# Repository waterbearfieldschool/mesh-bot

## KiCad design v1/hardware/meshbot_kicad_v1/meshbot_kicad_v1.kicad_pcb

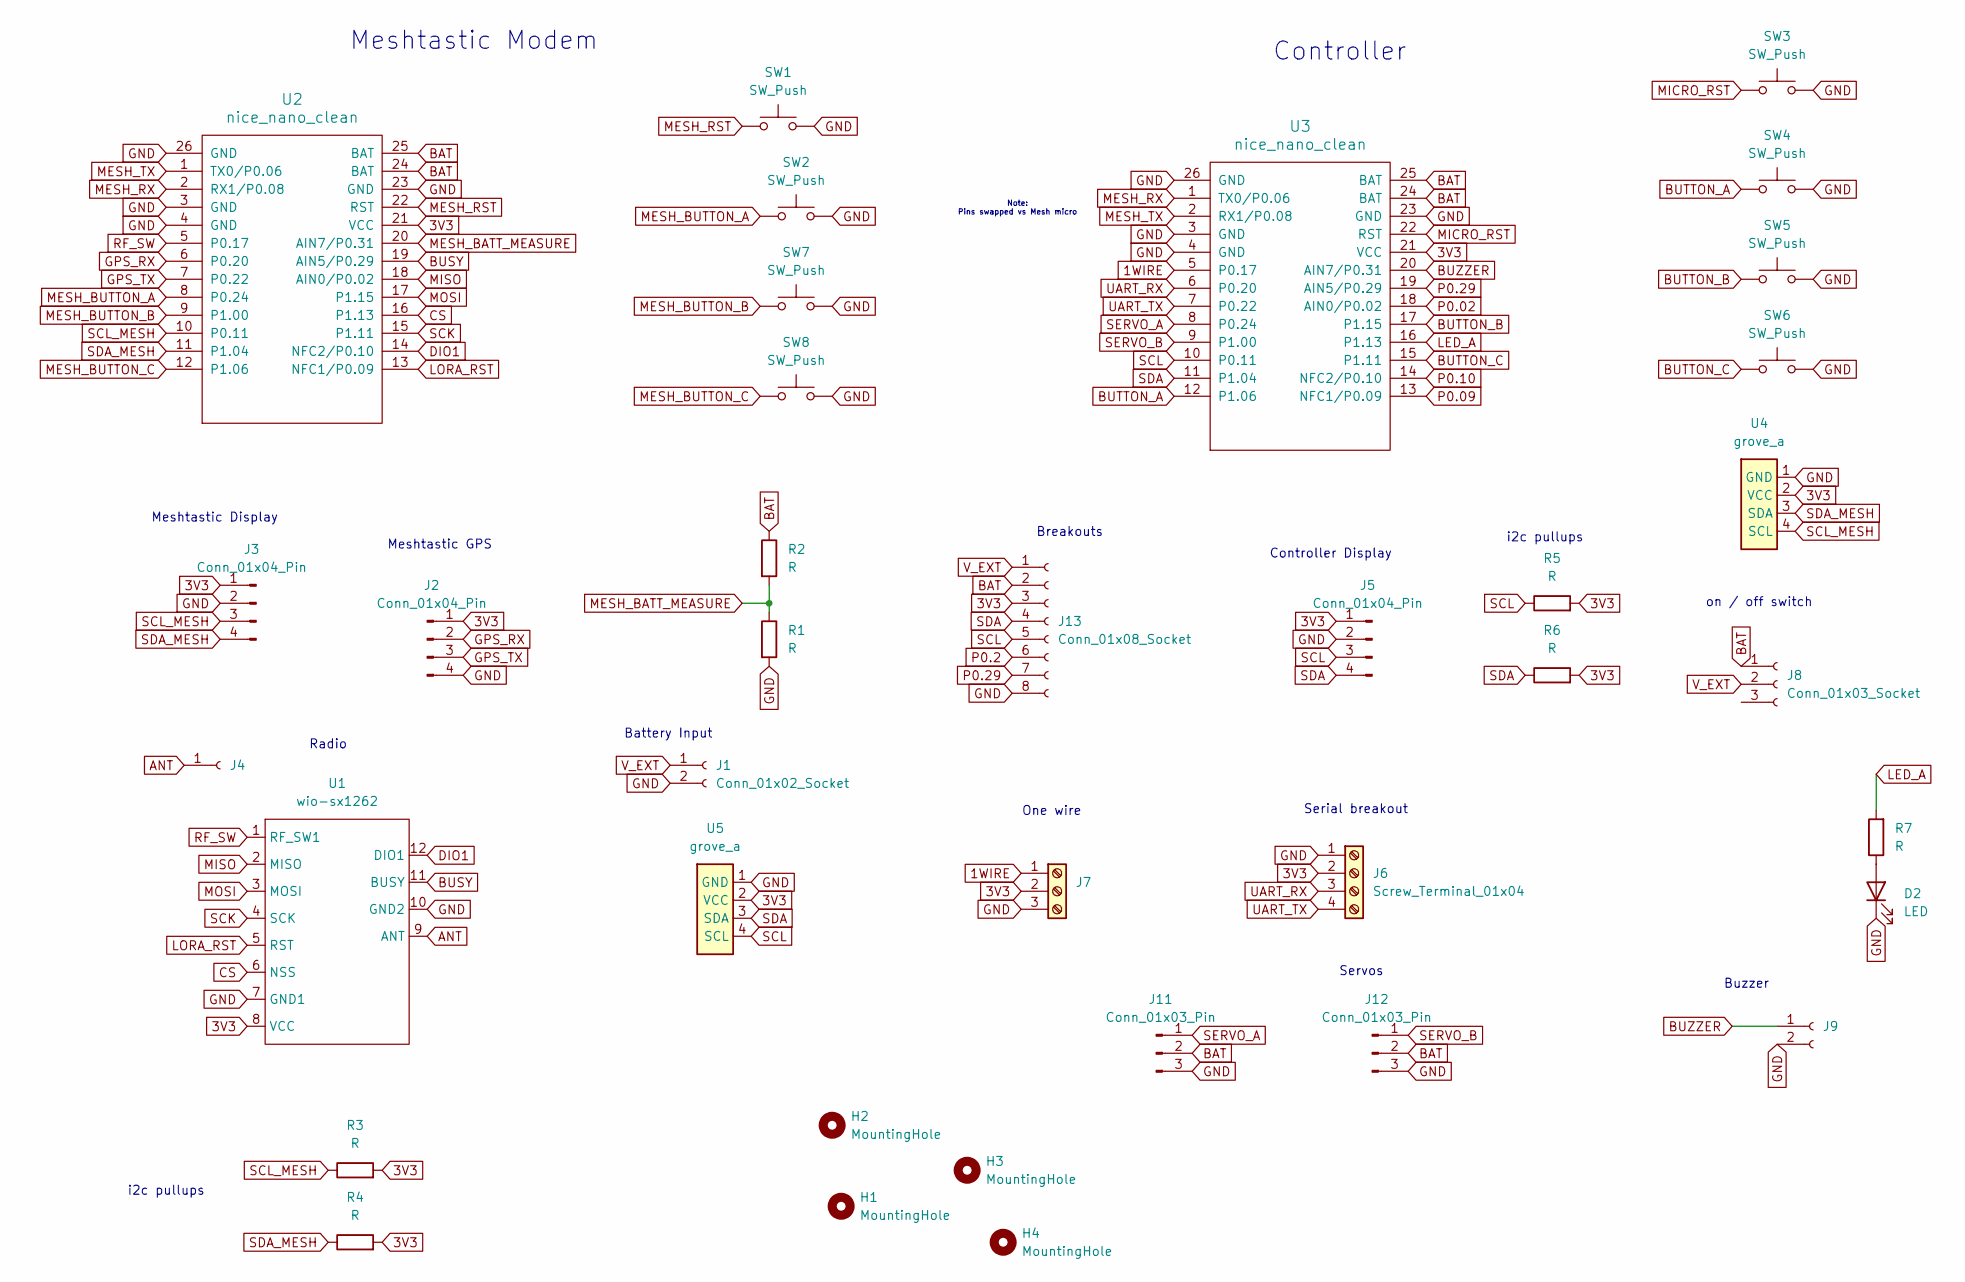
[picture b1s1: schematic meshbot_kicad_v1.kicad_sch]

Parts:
D2: LED; LED_D3.0mm
H1, H2, H3, H4: MountingHole; MountingHole_3.2mm_M3
J1: Conn_01x02_Socket; JST_PH_B2B-PH-K_1x02_P2.00mm_Vertical
J2: Conn_01x04_Pin; gps_ublox_blue
J3, J5: Conn_01x04_Pin; ssd1306_a
J4: Conn_01x01_Socket; PinSocket_1x01_P2.54mm_Vertical
J6: Screw_Terminal_01x04; TerminalBlock_Phoenix_MKDS-1,5-4-5.08_1x04_P5.08mm_Horizont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
J7: Screw_Terminal_01x03; TerminalBlock_Phoenix_MKDS-1,5-3-5.08_1x03_P5.08mm_Horizont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
J8: Conn_01x03_Socket; usual_switch
J9: Conn_01x02_Socket; Buzzer_12x9.5RM7.6
J11, J12: Conn_01x03_Pin; PinHeader_1x03_P2.54mm_Vertical
J13: Conn_01x08_Socket; PinSocket_1x08_P2.54mm_Vertical
R1, R2, R3, R4, R5, R6, R7: R; R_Axial_DIN0204_L3.6mm_D1.6mm_P1.90mm_Vertical
SW1, SW2, SW3, SW4, SW5, SW6, SW7, SW8: SW_Push; SW_Tactile_SPST_Angled_PTS645Vx31-2LFS
U1: wio-sx1262
U2, U3: nice_nano_clean; nice_nano_cleanest
U4: grove_a
U5: grove_a; grove_rightangle

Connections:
1WIRE: J7.1, U3.5 (P0.17)
3V3: J2.1, J3.1, J5.1, J6.2, J7.2, J13.3, R3.2, R4.2, R5.2, R6.2, U1.8 (VCC), U2.21 (VCC), U3.21 (VCC), U4.2 (VCC), U5.2 (VCC)
ANT: J4.1, U1.9 (ANT)
BAT: J8.1, J11.2, J12.2, J13.2, R2.1, U2.24 (BAT), U2.25 (BAT), U3.24 (BAT), U3.25 (BAT)
BUSY: U1.11 (BUSY), U2.19 (AIN5/P0.29)
BUTTON_A: SW4.1, U3.12 (P1.06)
BUTTON_B: SW5.1, U3.17 (P1.15)
BUTTON_C: SW6.1, U3.15 (P1.11)
BUZZER: J9.1, U3.20 (AIN7/P0.31)
CS: U1.6 (NSS), U2.16 (P1.13)
DIO1: U1.12 (DIO1), U2.14 (NFC2/P0.10)
GND: D2.1 (K), J1.2, J2.4, J3.2, J5.2, J6.1, J7.3, J9.2, J11.3, J12.3, J13.8, R1.2, SW1.2, SW2.2, SW3.2, SW4.2, SW5.2, SW6.2, SW7.2, SW8.2, U1.7 (GND1), U1.10 (GND2), U2.3 (GND), U2.4 (GND), U2.23 (GND), U2.26 (GND), U3.3 (GND), U3.4 (GND), U3.23 (GND), U3.26 (GND), U4.1 (GND), U5.1 (GND)
GPS_RX: J2.2, U2.6 (P0.20)
GPS_TX: J2.3, U2.7 (P0.22)
LED_A: R7.2, U3.16 (P1.13)
LORA_RST: U1.5 (RST), U2.13 (NFC1/P0.09)
MESH_BATT_MEASURE: R1.1, R2.2, U2.20 (AIN7/P0.31)
MESH_BUTTON_A: SW2.1, U2.8 (P0.24)
MESH_BUTTON_B: SW7.1, U2.9 (P1.00)
MESH_BUTTON_C: SW8.1, U2.12 (P1.06)
MESH_RST: SW1.1, U2.22 (RST)
MESH_RX: U2.2 (RX1/P0.08), U3.1 (TX0/P0.06)
MESH_TX: U2.1 (TX0/P0.06), U3.2 (RX1/P0.08)
MICRO_RST: SW3.1, U3.22 (RST)
MISO: U1.2 (MISO), U2.18 (AIN0/P0.02)
MOSI: U1.3 (MOSI), U2.17 (P1.15)
unnamed: D2.2 (A), R7.1
P0.02: U3.18 (AIN0/P0.02)
P0.2: J13.6
P0.09: U3.13 (NFC1/P0.09)
P0.10: U3.14 (NFC2/P0.10)
P0.29: J13.7, U3.19 (AIN5/P0.29)
RF_SW: U1.1 (RF_SW1), U2.5 (P0.17)
SCK: U1.4 (SCK), U2.15 (P1.11)
SCL: J5.3, J13.5, R5.1, U3.10 (P0.11), U5.4 (SCL)
SCL_MESH: J3.3, R3.1, U2.10 (P0.11), U4.4 (SCL)
SDA: J5.4, J13.4, R6.1, U3.11 (P1.04), U5.3 (SDA)
SDA_MESH: J3.4, R4.1, U2.11 (P1.04), U4.3 (SDA)
SERVO_A: J11.1, U3.8 (P0.24)
SERVO_B: J12.1, U3.9 (P1.00)
UART_RX: J6.3, U3.6 (P0.20)
UART_TX: J6.4, U3.7 (P0.22)
V_EXT: J1.1, J8.2, J13.1

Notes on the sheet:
Note: Pins swapped vs Mesh micro
Meshtastic GPS
Controller Display
Meshtastic Modem
Serial breakout
Buzzer
Controller
on / off switch
One wire
Breakouts
i2c pullups
Meshtastic Display
Radio
Battery Input
Servos

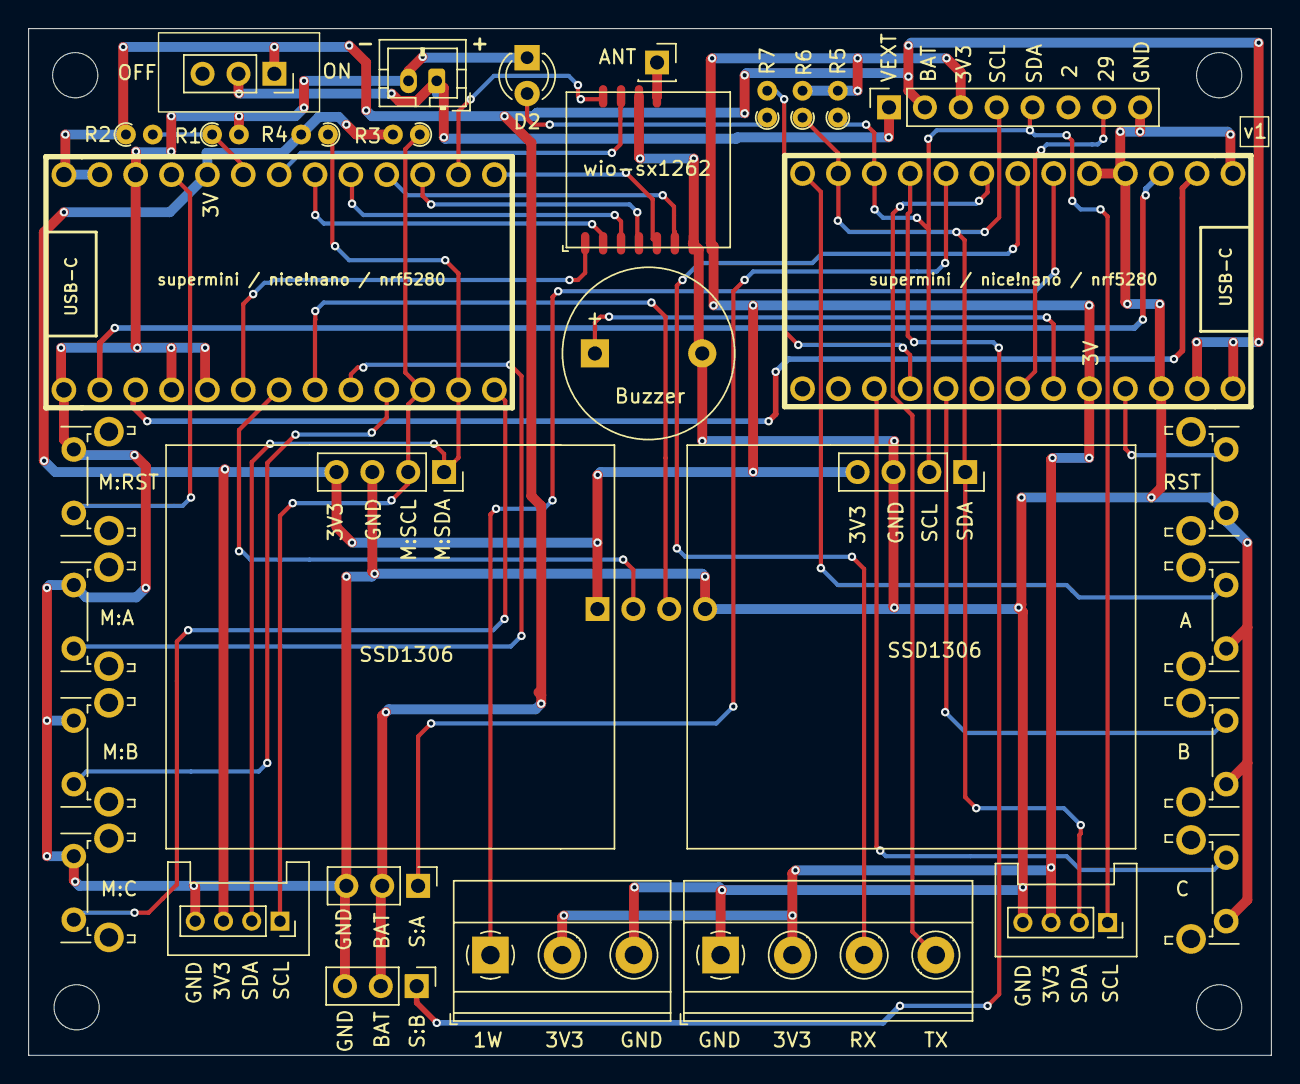
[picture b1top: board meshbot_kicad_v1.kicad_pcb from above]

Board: 2 copper layers, 88.0 x 72.7 mm, 37 parts (1 on the bottom side), 39 nets.

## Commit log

2025-07-02 routed power
